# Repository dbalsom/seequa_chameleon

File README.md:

# The Seequa Chameleon

The Chameleon was an interesting PC clone luggable. 

It had a Z80 and 8088 CPU, which could be switched between, allowing a Chameleon owner to use both MS-DOS and CP/M.

Forgoing the usual ISA expansion slots, it included a number of peripherals directly on the motherboard, including an integrated CGA-compatible video card with some interesting additions such as font SRAM and palette registers.

This project aims to produce schematics for the Chameleon by tracing out the motherboard in Kicad.

## Requirements

This project requires [KiCad version 9](https://www.kicad.org/download/).

## More info

For more info on the Chameleon, see the excellent [seequa.org](https://seequa.org/)

## Special Thanks

Thanks to Matthew Jones for nerd-sniping me with this fascinating and wonky machine.

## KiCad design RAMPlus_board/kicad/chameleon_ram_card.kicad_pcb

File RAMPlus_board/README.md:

# Seequa Chameleon RAMPlus Expansion Board

This repository contains a KiCad project that reproduces the Seequa Chameleon RAMPlus expansion board, P/N 050051 REV C. 

This board has not yet been ordered and tested, but it does pass all design and electrical rule checks. If you want to be the first to try it, be my guest, but I make no guarantees there will be no bodges required. There almost certainly will be some issue I have missed.

This board will not function without the required PAL chips - so you will need a source for those. I hope to eventually figure out how to replace the PALs with a GAL or some other kind of PLD.

## Details and Modifications to the Original 

* **UART Option:** The current version of this board does not include the 8250 UART option found on some versions of the RAMPlus card.

* **Power Connections:** A screw terminal footprint has been added for power wiring if you'd like your board to be removable without fishing the molex plug out from the guts of your Chameleon, or if your power leads have broken off or otherwise detached.

  I am not sure what screw terminals will work given the tight clearances involved - when this has been verified I will update this README.

  The original strain relief pass-through holes and pads are still present if you would prefer to use them, and have been reinforced with plated through-holes and stitched copper fills for improved durability.

* **Parity RAM Jumper:** A new jumper J2 has been introduced. This allows configuration to skip populating the parity RAM chips if parity checking is not required.  Jumper pins 1&2 to enable parity, jumper pins 2&3 to disable it. This is independent of any software parity control.

* **Minor improvements:**
  * Where possible, ground and power traces have been enlarged. 
  * The footprints for the mounting posts have had their pads enlarged.
  * The strain-relief pass-through holes have been moved further way from the edge of the board.
  * The lower-right mounting post has been grounded.

## BOM 

The authoritative BOM should ideally be generated in KiCad, but RAMPlus_BOM.csv has been exported for your reference.
If you do plan to order one of these boards, please get in touch first to make sure there are no last minute updates that have not been reflected here.

## Sourcing Components

Some components may be difficult to find. The particular type of three-legged trimmer capacitor used to adjust the RTC crystal timing is no longer manufactured. Surplus trimmer caps are still available. One site selling them is here (no afffiliation or recommendation implied, caveat emptor):

https://www.surplussales.com/items/106928/ceramic-trimmer-capacitor/

The MM58167 RTC chip can regularly be found on eBay.

The board may be able to use 4164 DRAMs with some tweaks to capacitor values - Seequa populated the board with 4564s, which you can find on eBay or in bulk here:
https://www.electronicsurplus.com/mostek-mk4564n15-ic-memory-dram-64k-x-1
https://www.surplussales.com/items/147639/mostek-memory-dip/

## PALs

The RAMPlus card includes two new PALs, a DRAM decoder for the three new RAM banks, and an address decoder / control PAL for the RTC. These have yet to be dumped, but will be in time.

The RAMPlus w/ Serial option has a third PAL, SERB, to decode for the 8250.

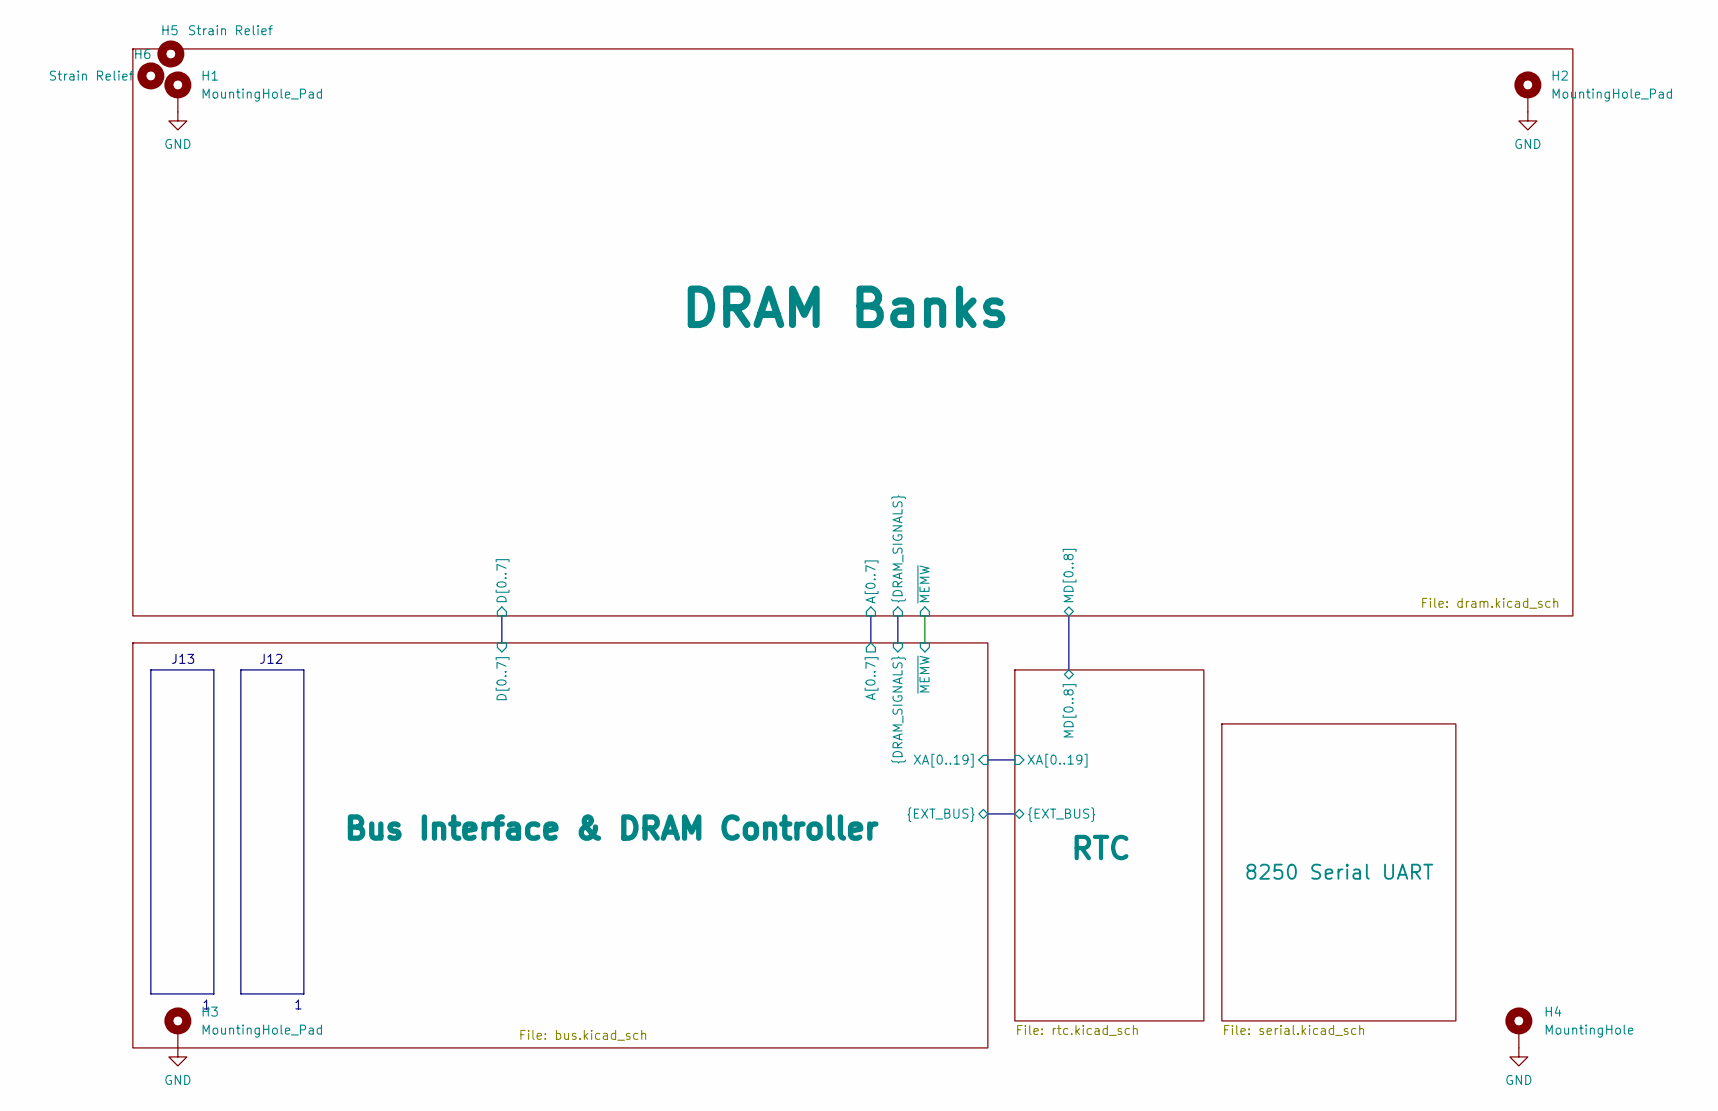
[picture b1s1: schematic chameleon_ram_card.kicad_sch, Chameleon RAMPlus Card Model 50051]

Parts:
H1, H2, H3: MountingHole_Pad; MountingHole_3.2mm_M3_Pad_TopBottom
H4: MountingHole; MountingHole_3.2mm_M3_Pad_TopBottom
H5, H6: Strain Relief; StrainRelief_LoopHole_2.7mm_PTH

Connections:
GND: H1.1, H2.1, H3.1, H4.1; also elsewhere on the board

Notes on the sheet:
J12
J13

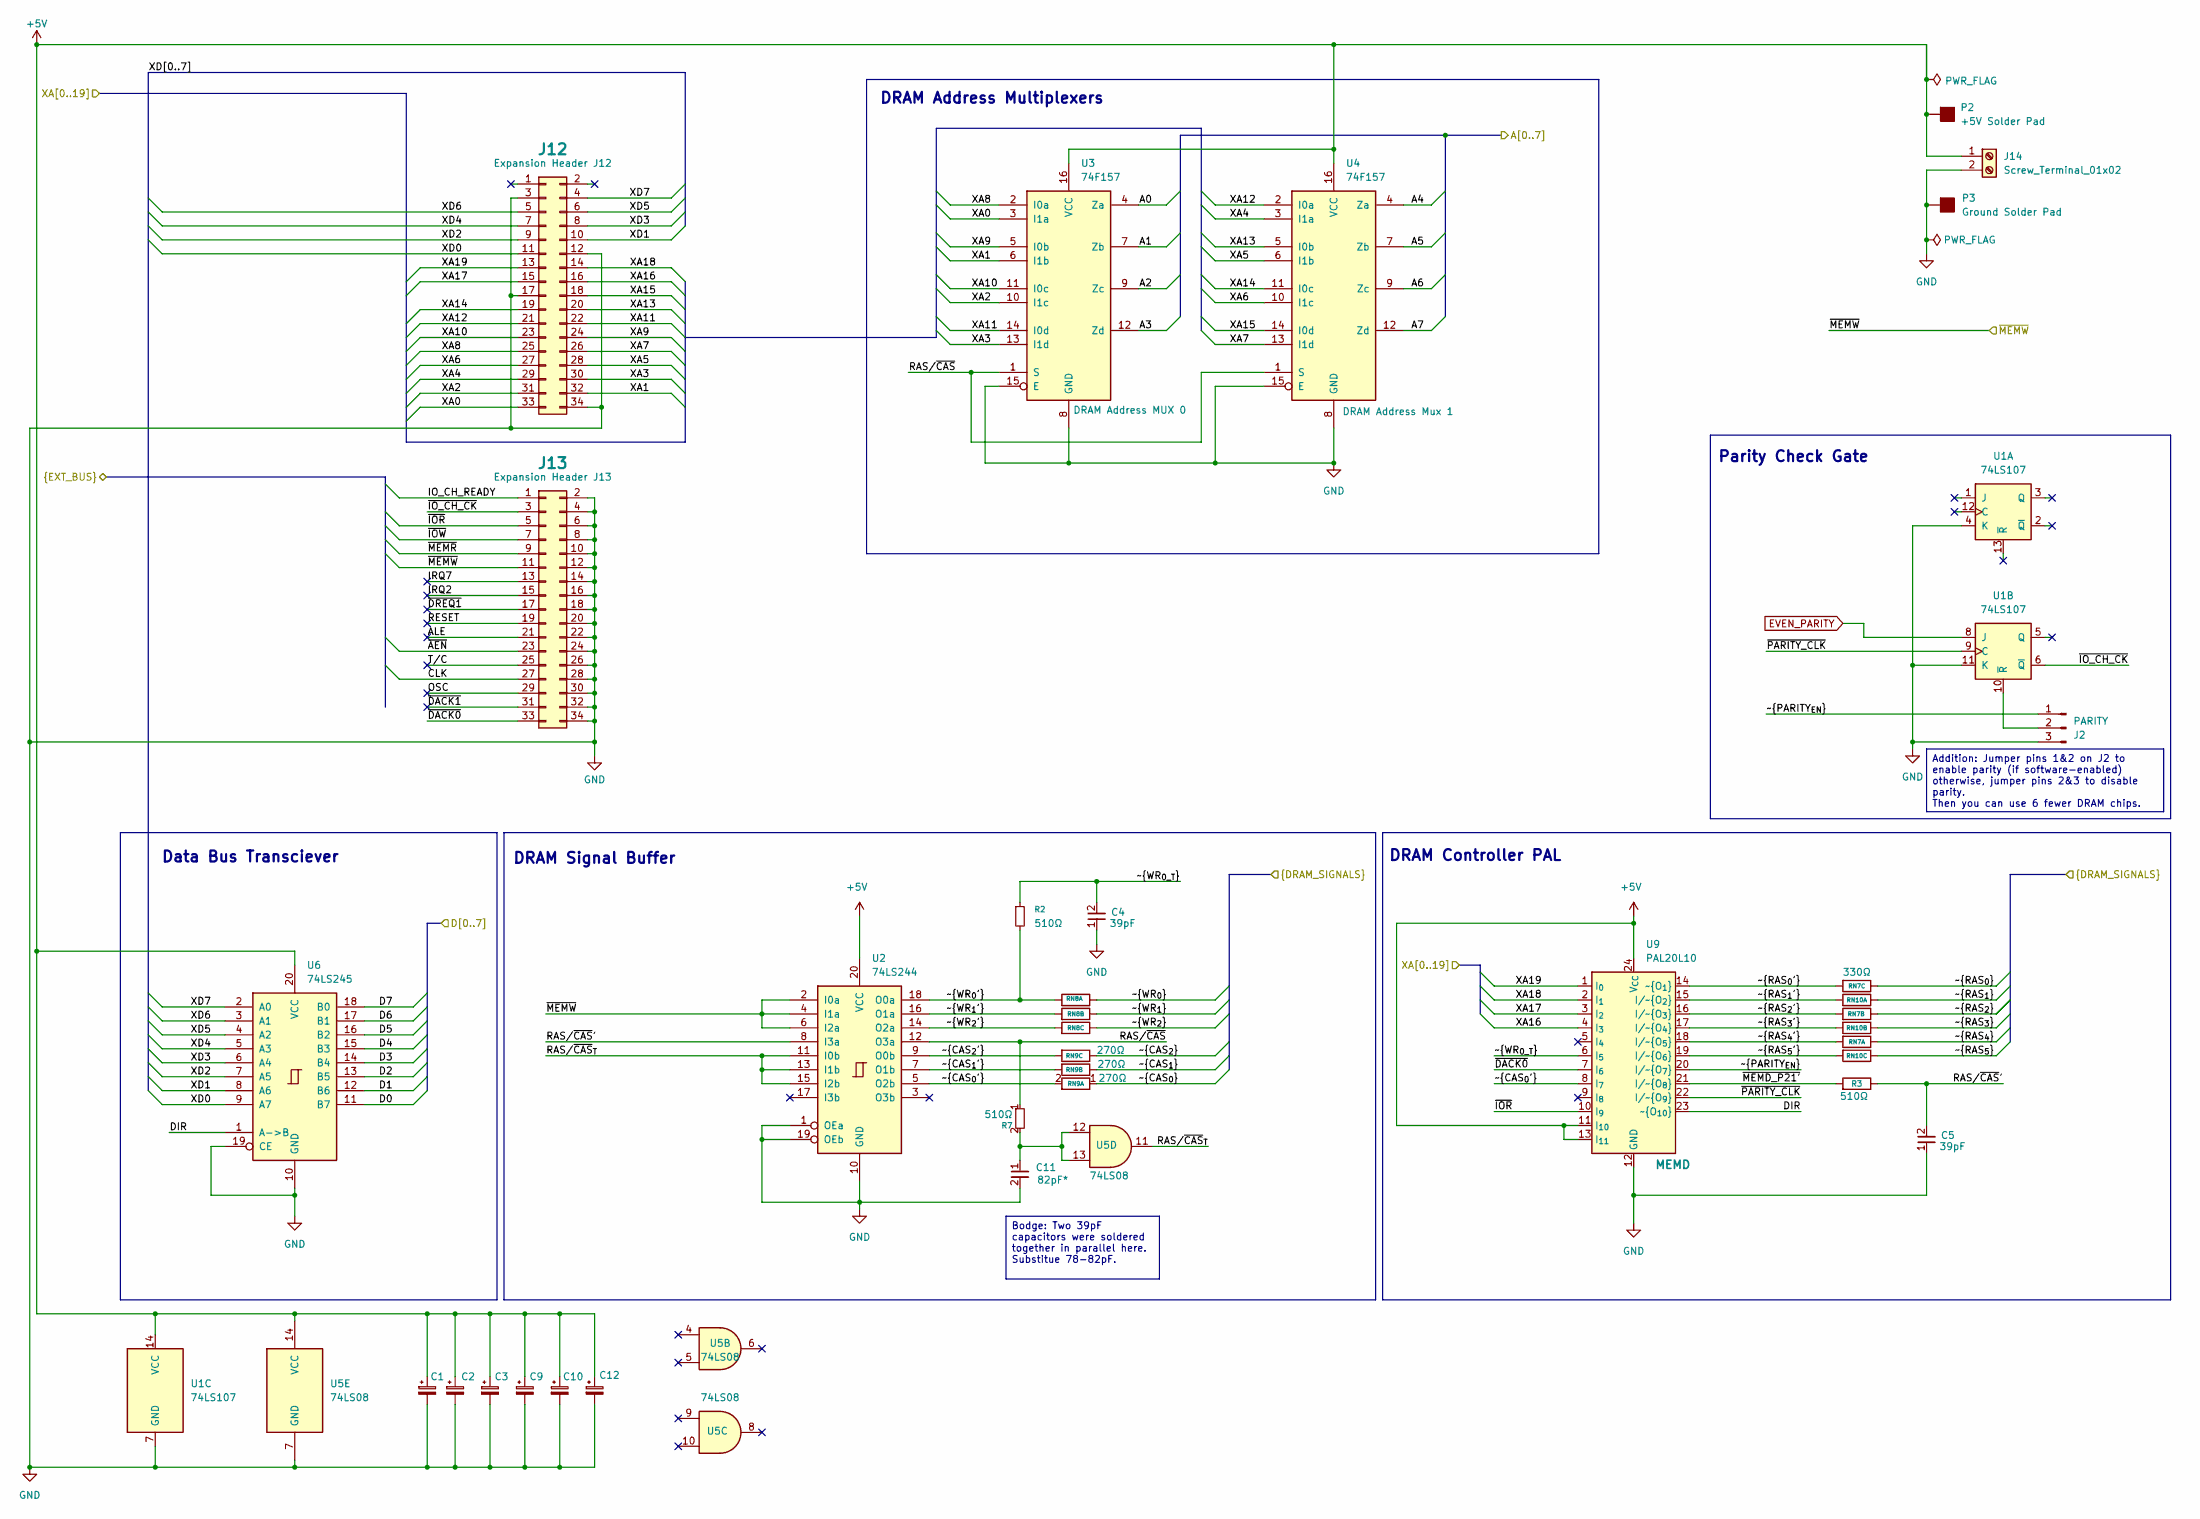
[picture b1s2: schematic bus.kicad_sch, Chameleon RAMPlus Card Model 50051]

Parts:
C1, C2, C3, C9, C10, C12: 0.1uF; C_Seequa_Dipped_Tantalum_P7.50
C4, C5: 39pF; C_Seequa_Disc_P7.50mm
C11: 82pF*; C_Seequa_Disc_P7.50mm
J2: PARITY; PinHeader_1x03_P2.54mm_Vertical
J12: Expansion Header J12; PinHeader_2x17_P2.54mm_Vertical
J13: Expansion Header J13; PinHeader_2x17_P2.54mm_Vertical
J14: Screw_Terminal_01x02; TerminalBlock_Phoenix_MKDS-1,5-2-5.08_1x02_P5.08mm_Horizont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
P2: +5V Solder Pad; Power_Pad_2.0x2.0mm
P3: Ground Solder Pad; Power_Pad_2.0x2.0mm
R2, R3, R7: 510Ω; R_Seequa_P10_7.5mm_Box
RN7, RN8: 330Ω; R_Array_SIP6_Compact
RN9: 270Ω; R_Array_SIP6_Compact
RN10: 330Ω; R_Array_SIP6
U1: 74LS107; DIP-14_W7.62mm_Socket
U2: 74LS244; DIP-20_W7.62mm_Socket
U3, U4: 74F157; DIP-16_W7.62mm_Socket
U5: 74LS08; DIP-14_W7.62mm_Socket
U6: 74LS245; DIP-20_W7.62mm_Socket
U9: PAL20L10; DIP-24_W7.62mm_Socket

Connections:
+5V: C1.1, C2.1, C3.1, C9.1, C10.1, C12.1, J14.1, P2.1, U1.14 (VCC), U2.20 (VCC), U3.16 (VCC), U4.16 (VCC), U5.14 (VCC), U6.20 (VCC), U9.11 (I_{10}), U9.13 (I_{11}), U9.24 (V_{CC}); also elsewhere on the board
/Bus Interface & DRAM Controller/A0: U3.4 (Za); also elsewhere on the board
/Bus Interface & DRAM Controller/A1: U3.7 (Zb); also elsewhere on the board
/Bus Interface & DRAM Controller/A2: U3.9 (Zc); also elsewhere on the board
/Bus Interface & DRAM Controller/A3: U3.12 (Zd); also elsewhere on the board
/Bus Interface & DRAM Controller/A4: U4.4 (Za); also elsewhere on the board
/Bus Interface & DRAM Controller/A5: U4.7 (Zb); also elsewhere on the board
/Bus Interface & DRAM Controller/A6: U4.9 (Zc); also elsewhere on the board
/Bus Interface & DRAM Controller/A7: U4.12 (Zd); also elsewhere on the board
/Bus Interface & DRAM Controller/CLK: J13.27 (CLK); also elsewhere on the board
/Bus Interface & DRAM Controller/D0: U6.11 (B7); also elsewhere on the board
/Bus Interface & DRAM Controller/D1: U6.12 (B6); also elsewhere on the board
/Bus Interface & DRAM Controller/D2: U6.13 (B5); also elsewhere on the board
/Bus Interface & DRAM Controller/D3: U6.14 (B4); also elsewhere on the board
/Bus Interface & DRAM Controller/D4: U6.15 (B3); also elsewhere on the board
/Bus Interface & DRAM Controller/D5: U6.16 (B2); also elsewhere on the board
/Bus Interface & DRAM Controller/D6: U6.17 (B1); also elsewhere on the board
/Bus Interface & DRAM Controller/D7: U6.18 (B0); also elsewhere on the board
/Bus Interface & DRAM Controller/DIR: U6.1 (A->B), U9.23 (~O_{10})
/Bus Interface & DRAM Controller/IO_CH_READY: J13.1 (IO_CH_READY); also elsewhere on the board
/Bus Interface & DRAM Controller/RAS/~CAS: R7.1, U2.12 (O3a), U3.1 (S), U4.1 (S)
/Bus Interface & DRAM Controller/RAS/~CAS': C5.2, R3.1, U2.8 (I3a)
/Bus Interface & DRAM Controller/RAS/~CAS_{T}: U2.11 (I0b), U2.13 (I1b), U2.15 (I2b), U5.11
/Bus Interface & DRAM Controller/XA0: J12.33 (A0), U3.3 (I1a); also elsewhere on the board
/Bus Interface & DRAM Controller/XA1: J12.32 (A1), U3.6 (I1b); also elsewhere on the board
/Bus Interface & DRAM Controller/XA2: J12.31 (A2), U3.10 (I1c); also elsewhere on the board
/Bus Interface & DRAM Controller/XA3: J12.30 (A3), U3.13 (I1d); also elsewhere on the board
/Bus Interface & DRAM Controller/XA4: J12.29 (A4), U4.3 (I1a); also elsewhere on the board
/Bus Interface & DRAM Controller/XA5: J12.28 (A5), U4.6 (I1b); also elsewhere on the board
/Bus Interface & DRAM Controller/XA6: J12.27 (A6), U4.10 (I1c); also elsewhere on the board
/Bus Interface & DRAM Controller/XA7: J12.26 (A7), U4.13 (I1d); also elsewhere on the board
/Bus Interface & DRAM Controller/XA8: J12.25 (A8), U3.2 (I0a); also elsewhere on the board
/Bus Interface & DRAM Controller/XA9: J12.24 (A9), U3.5 (I0b); also elsewhere on the board
/Bus Interface & DRAM Controller/XA10: J12.23 (A10), U3.11 (I0c); also elsewhere on the board
/Bus Interface & DRAM Controller/XA11: J12.22 (A11), U3.14 (I0d)
/Bus Interface & DRAM Controller/XA12: J12.21 (A12), U4.2 (I0a)
/Bus Interface & DRAM Controller/XA13: J12.20 (A13), U4.5 (I0b)
/Bus Interface & DRAM Controller/XA14: J12.19 (A14), U4.11 (I0c)
/Bus Interface & DRAM Controller/XA15: J12.18 (A15), U4.14 (I0d)
/Bus Interface & DRAM Controller/XA16: J12.16 (A16), U9.4 (I_{3})
/Bus Interface & DRAM Controller/XA17: J12.15 (A17), U9.3 (I_{2})
/Bus Interface & DRAM Controller/XA18: J12.14 (A18), U9.2 (I_{1})
/Bus Interface & DRAM Controller/XA19: J12.13 (A19), U9.1 (I_{0})
/Bus Interface & DRAM Controller/XD0: J12.11 (D0), U6.9 (A7)
/Bus Interface & DRAM Controller/XD1: J12.10 (D1), U6.8 (A6)
/Bus Interface & DRAM Controller/XD2: J12.9 (D2), U6.7 (A5)
/Bus Interface & DRAM Controller/XD3: J12.8 (D3), U6.6 (A4)
/Bus Interface & DRAM Controller/XD4: J12.7 (D4), U6.5 (A3)
/Bus Interface & DRAM Controller/XD5: J12.6 (D5), U6.4 (A2)
/Bus Interface & DRAM Controller/XD6: J12.5 (D6), U6.3 (A1)
/Bus Interface & DRAM Controller/XD7: J12.4 (D7), U6.2 (A0)
/Bus Interface & DRAM Controller/~AEN: J13.23 (~AEN); also elsewhere on the board
/Bus Interface & DRAM Controller/~CAS_{0'}: RN9.2 (R1.2), U2.5 (O2b), U9.8 (I_{7})
/Bus Interface & DRAM Controller/~CAS_{0}: RN9.1 (R1.1); also elsewhere on the board
/Bus Interface & DRAM Controller/~CAS_{1'}: RN9.4 (R2.2), U2.7 (O1b)
/Bus Interface & DRAM Controller/~CAS_{1}: RN9.3 (R2.1); also elsewhere on the board
/Bus Interface & DRAM Controller/~CAS_{2'}: RN9.6 (R3.2), U2.9 (O0b)
/Bus Interface & DRAM Controller/~CAS_{2}: RN9.5 (R3.1); also elsewhere on the board
/Bus Interface & DRAM Controller/~DACK0: J13.33 (~DACK0), U9.7 (I_{6})
/Bus Interface & DRAM Controller/~IOR: J13.5 (~IOR), U9.10 (I_{9})
/Bus Interface & DRAM Controller/~IOW: J13.7 (~IOW); also elsewhere on the board
/Bus Interface & DRAM Controller/~IO_CH_CK: J13.3 (~IO_CH_CK), U1.6 (~Q)
/Bus Interface & DRAM Controller/~MEMD_P21': R3.2, U9.21 (I/~O_{8})
/Bus Interface & DRAM Controller/~MEMR: J13.9 (~MEMR); also elsewhere on the board
/Bus Interface & DRAM Controller/~MEMW: J13.11 (~MEMW), U2.2 (I0a), U2.4 (I1a), U2.6 (I2a); also elsewhere on the board
/Bus Interface & DRAM Controller/~PARITY_CLK: U1.9 (C), U9.22 (I/~O_{9})
/Bus Interface & DRAM Controller/~PARITY_{EN}: J2.1, U9.20 (I/~O_{7})
/Bus Interface & DRAM Controller/~RAS_{0'}: RN7.6 (R3.2), U9.14 (~O_{1})
/Bus Interface & DRAM Controller/~RAS_{0}: RN7.5 (R3.1); also elsewhere on the board
/Bus Interface & DRAM Controller/~RAS_{1'}: RN10.2 (R1.2), U9.15 (I/~O_{2})
/Bus Interface & DRAM Controller/~RAS_{1}: RN10.1 (R1.1); also elsewhere on the board
/Bus Interface & DRAM Controller/~RAS_{2'}: RN7.4 (R2.2), U9.16 (I/~O_{3})
/Bus Interface & DRAM Controller/~RAS_{2}: RN7.3 (R2.1); also elsewhere on the board
/Bus Interface & DRAM Controller/~RAS_{3'}: RN10.4 (R2.2), U9.17 (I/~O_{4})
/Bus Interface & DRAM Controller/~RAS_{3}: RN10.3 (R2.1); also elsewhere on the board
/Bus Interface & DRAM Controller/~RAS_{4'}: RN7.2 (R1.2), U9.18 (I/~O_{5})
/Bus Interface & DRAM Controller/~RAS_{4}: RN7.1 (R1.1); also elsewhere on the board
/Bus Interface & DRAM Controller/~RAS_{5'}: RN10.6 (R3.2), U9.19 (I/~O_{6})
/Bus Interface & DRAM Controller/~RAS_{5}: RN10.5 (R3.1); also elsewhere on the board
/Bus Interface & DRAM Controller/~WR_{0_T}: C4.2, R2.1, U9.6 (I_{5})
/Bus Interface & DRAM Controller/~WR_{0'}: R2.2, RN8.2 (R1.2), U2.18 (O0a)
/Bus Interface & DRAM Controller/~WR_{0}: RN8.1 (R1.1); also elsewhere on the board
/Bus Interface & DRAM Controller/~WR_{1'}: RN8.4 (R2.2), U2.16 (O1a)
/Bus Interface & DRAM Controller/~WR_{1}: RN8.3 (R2.1); also elsewhere on the board
/Bus Interface & DRAM Controller/~WR_{2'}: RN8.6 (R3.2), U2.14 (O2a)
/Bus Interface & DRAM Controller/~WR_{2}: RN8.5 (R3.1); also elsewhere on the board
/Bus Interface &amp; DRAM Controller/ALE: J13.21 (ALE)
/Bus Interface &amp; DRAM Controller/IRQ2: J13.15 (IRQ2)
/Bus Interface &amp; DRAM Controller/IRQ7: J13.13 (IRQ7)
/Bus Interface &amp; DRAM Controller/OSC: J13.29 (OSC)
/Bus Interface &amp; DRAM Controller/RESET: J13.19 (RESET)
/Bus Interface &amp; DRAM Controller/T/C: J13.25 (T/C)
/Bus Interface &amp; DRAM Controller/~DACK1: J13.31 (~DACK1)
/Bus Interface &amp; DRAM Controller/~DREQ1: J13.17 (~DREQ1)
EVEN_PARITY: U1.8 (J); also elsewhere on the board
GND: C1.2, C2.2, C3.2, C4.1, C5.1, C9.2, C10.2, C11.2, C12.2, J2.3, J12.3 (GND), J12.12 (GND), J12.17 (GND), J12.34 (GND), J13.2 (GND), J13.4 (GND), J13.6 (GND), J13.8 (GND), J13.10 (GND), J13.12 (GND), J13.14 (GND), J13.16 (GND), J13.18 (GND), J13.20 (GND), J13.22 (GND), J13.24 (GND), J13.26 (GND), J13.28 (GND), J13.30 (GND), J13.32 (GND), J13.34 (GND), J14.2, P3.1, U1.4 (K), U1.7 (GND), U1.11 (K), U2.1 (OEa), U2.10 (GND), U2.19 (OEb), U3.8 (GND), U3.15 (E), U4.8 (GND), U4.15 (E), U5.7 (GND), U6.10 (GND), U6.19 (CE), U9.12 (GND); also elsewhere on the board
unnamed: C11.1, R7.2, U5.12, U5.13
unnamed: J2.2, U1.10 (~R)

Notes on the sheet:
DRAM Controller PAL
DRAM Address Multiplexers
Parity Check Gate
Data Bus Transciever
DRAM Signal Buffer
Addition: Jumper pins 1&2 on J2 to enable parity (if software-enabled) otherwise, jumper pins 2&3 to disable parity. Then you can use 6 fewer DRAM chips.
Bodge: Two 39pF capacitors were soldered together in parallel here. Substitue 78-82pF.

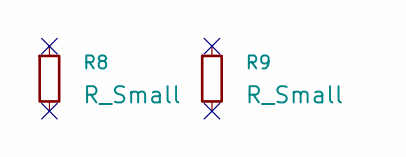
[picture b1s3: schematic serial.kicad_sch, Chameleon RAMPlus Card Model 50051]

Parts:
R8, R9: R_Small; R_Seequa_P10_7.5mm_Box

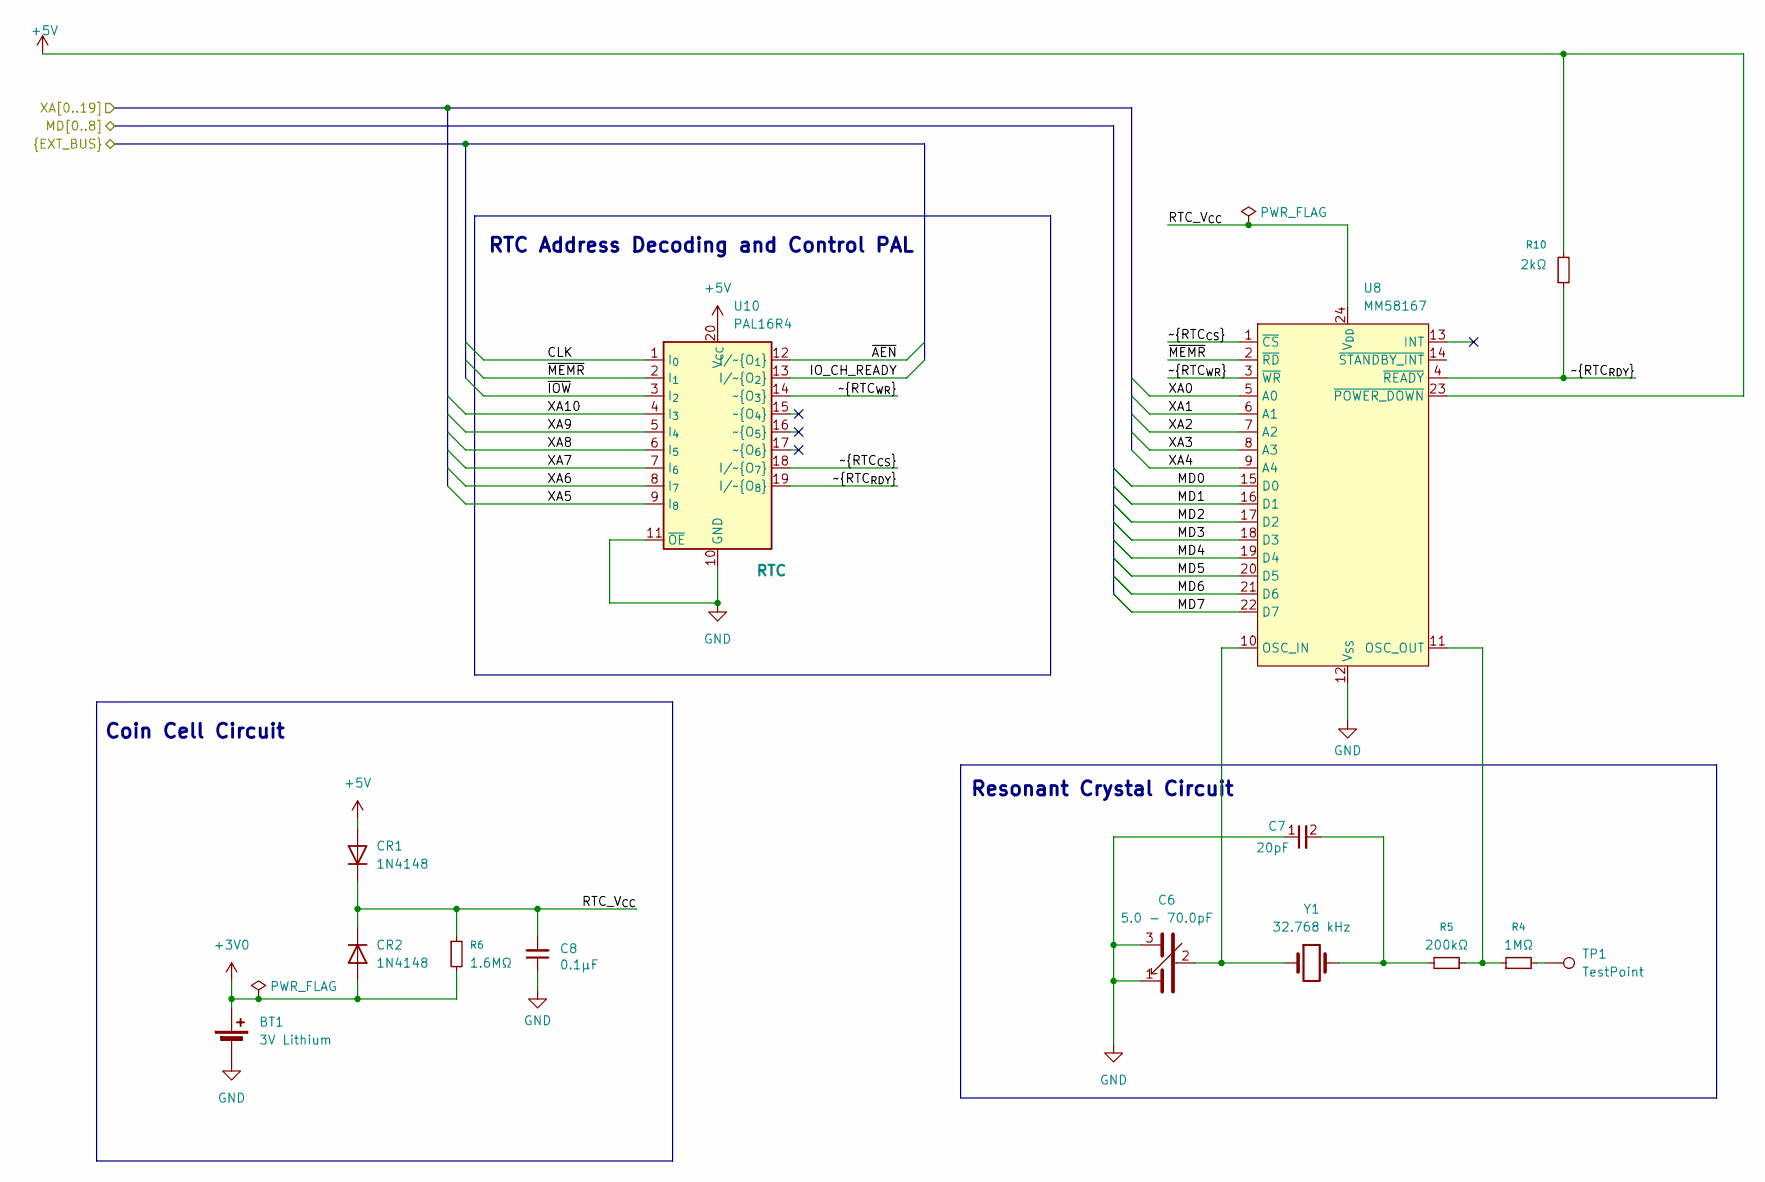
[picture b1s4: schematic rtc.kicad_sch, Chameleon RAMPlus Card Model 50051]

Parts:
BT1: 3V Lithium; Seequa_BatteryHolder_CR2032
C6: 5.0 - 70.0pF; C_Seequa_Trimmer
C7: 20pF; C_Seequa_Dipped_Film_P7.50mm
C8: 0.1µF; C_Seequa_Disc_P7.50mm
CR1, CR2: 1N4148; R_Seequa_P10_7.5mm_Box
R4: 1MΩ; R_Seequa_P10_7.5mm_Box
R5: 200kΩ; R_Seequa_P10_7.5mm_Box
R6: 1.6MΩ; R_Seequa_P10_7.5mm_Box
R10: 2kΩ; R_Seequa_P10_7.5mm_Box
TP1: TestPoint; TestPoint_THTPad_1.5x1.5mm_Drill0.7mm
U8: MM58167; DIP-24_W15.24mm_Socketed_Chip
U10: PAL16R4; DIP-20_W7.62mm_Socket
Y1: 32.768 kHz; Crystal_AT310_D3.0mm_L10.0mm_Vertical

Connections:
+3V0: BT1.1 (+), CR2.2 (A), R6.2
+5V: CR1.2 (A), R10.2, U8.23 (~POWER_DOWN), U10.20 (V_{CC}); also elsewhere on the board
/Bus Interface & DRAM Controller/CLK: U10.1 (I_{0}); also elsewhere on the board
/Bus Interface & DRAM Controller/IO_CH_READY: U10.13 (I/~O_{2}); also elsewhere on the board
/Bus Interface & DRAM Controller/XA0: U8.5 (A0); also elsewhere on the board
/Bus Interface & DRAM Controller/XA1: U8.6 (A1); also elsewhere on the board
/Bus Interface & DRAM Controller/XA2: U8.7 (A2); also elsewhere on the board
/Bus Interface & DRAM Controller/XA3: U8.8 (A3); also elsewhere on the board
/Bus Interface & DRAM Controller/XA4: U8.9 (A4); also elsewhere on the board
/Bus Interface & DRAM Controller/XA5: U10.9 (I_{8}); also elsewhere on the board
/Bus Interface & DRAM Controller/XA6: U10.8 (I_{7}); also elsewhere on the board
/Bus Interface & DRAM Controller/XA7: U10.7 (I_{6}); also elsewhere on the board
/Bus Interface & DRAM Controller/XA8: U10.6 (I_{5}); also elsewhere on the board
/Bus Interface & DRAM Controller/XA9: U10.5 (I_{4}); also elsewhere on the board
/Bus Interface & DRAM Controller/XA10: U10.4 (I_{3}); also elsewhere on the board
/Bus Interface & DRAM Controller/~AEN: U10.12 (I/~O_{1}); also elsewhere on the board
/Bus Interface & DRAM Controller/~IOW: U10.3 (I_{2}); also elsewhere on the board
/Bus Interface & DRAM Controller/~MEMR: U8.2 (~RD), U10.2 (I_{1}); also elsewhere on the board
/DRAM Banks/MD0: U8.15 (D0); also elsewhere on the board
/DRAM Banks/MD1: U8.16 (D1); also elsewhere on the board
/DRAM Banks/MD2: U8.17 (D2); also elsewhere on the board
/DRAM Banks/MD3: U8.18 (D3); also elsewhere on the board
/DRAM Banks/MD4: U8.19 (D4); also elsewhere on the board
/DRAM Banks/MD5: U8.20 (D5); also elsewhere on the board
/DRAM Banks/MD6: U8.21 (D6); also elsewhere on the board
/DRAM Banks/MD7: U8.22 (D7); also elsewhere on the board
/RTC/RTC_V_{CC}: C8.2, CR1.1 (K), CR2.1 (K), R6.1, U8.24 (V_{DD})
/RTC/~RTC_{CS}: U8.1 (~CS), U10.18 (I/~O_{7})
/RTC/~RTC_{RDY}: R10.1, U8.4 (~READY), U10.19 (I/~O_{8})
/RTC/~RTC_{WR}: U8.3 (~WR), U10.14 (~O_{3})
GND: BT1.2 (-), C6.1, C6.3, C7.1, C8.1, U8.12 (V_{SS}), U10.10 (GND), U10.11 (~OE); also elsewhere on the board
unnamed: C7.2, R5.2, Y1.2
unnamed: R4.2, TP1.1
unnamed: C6.2, U8.10 (OSC_IN), Y1.1
unnamed: R4.1, R5.1, U8.11 (OSC_OUT)

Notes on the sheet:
Coin Cell Circuit
RTC Address Decoding and Control PAL
Resonant Crystal Circuit
